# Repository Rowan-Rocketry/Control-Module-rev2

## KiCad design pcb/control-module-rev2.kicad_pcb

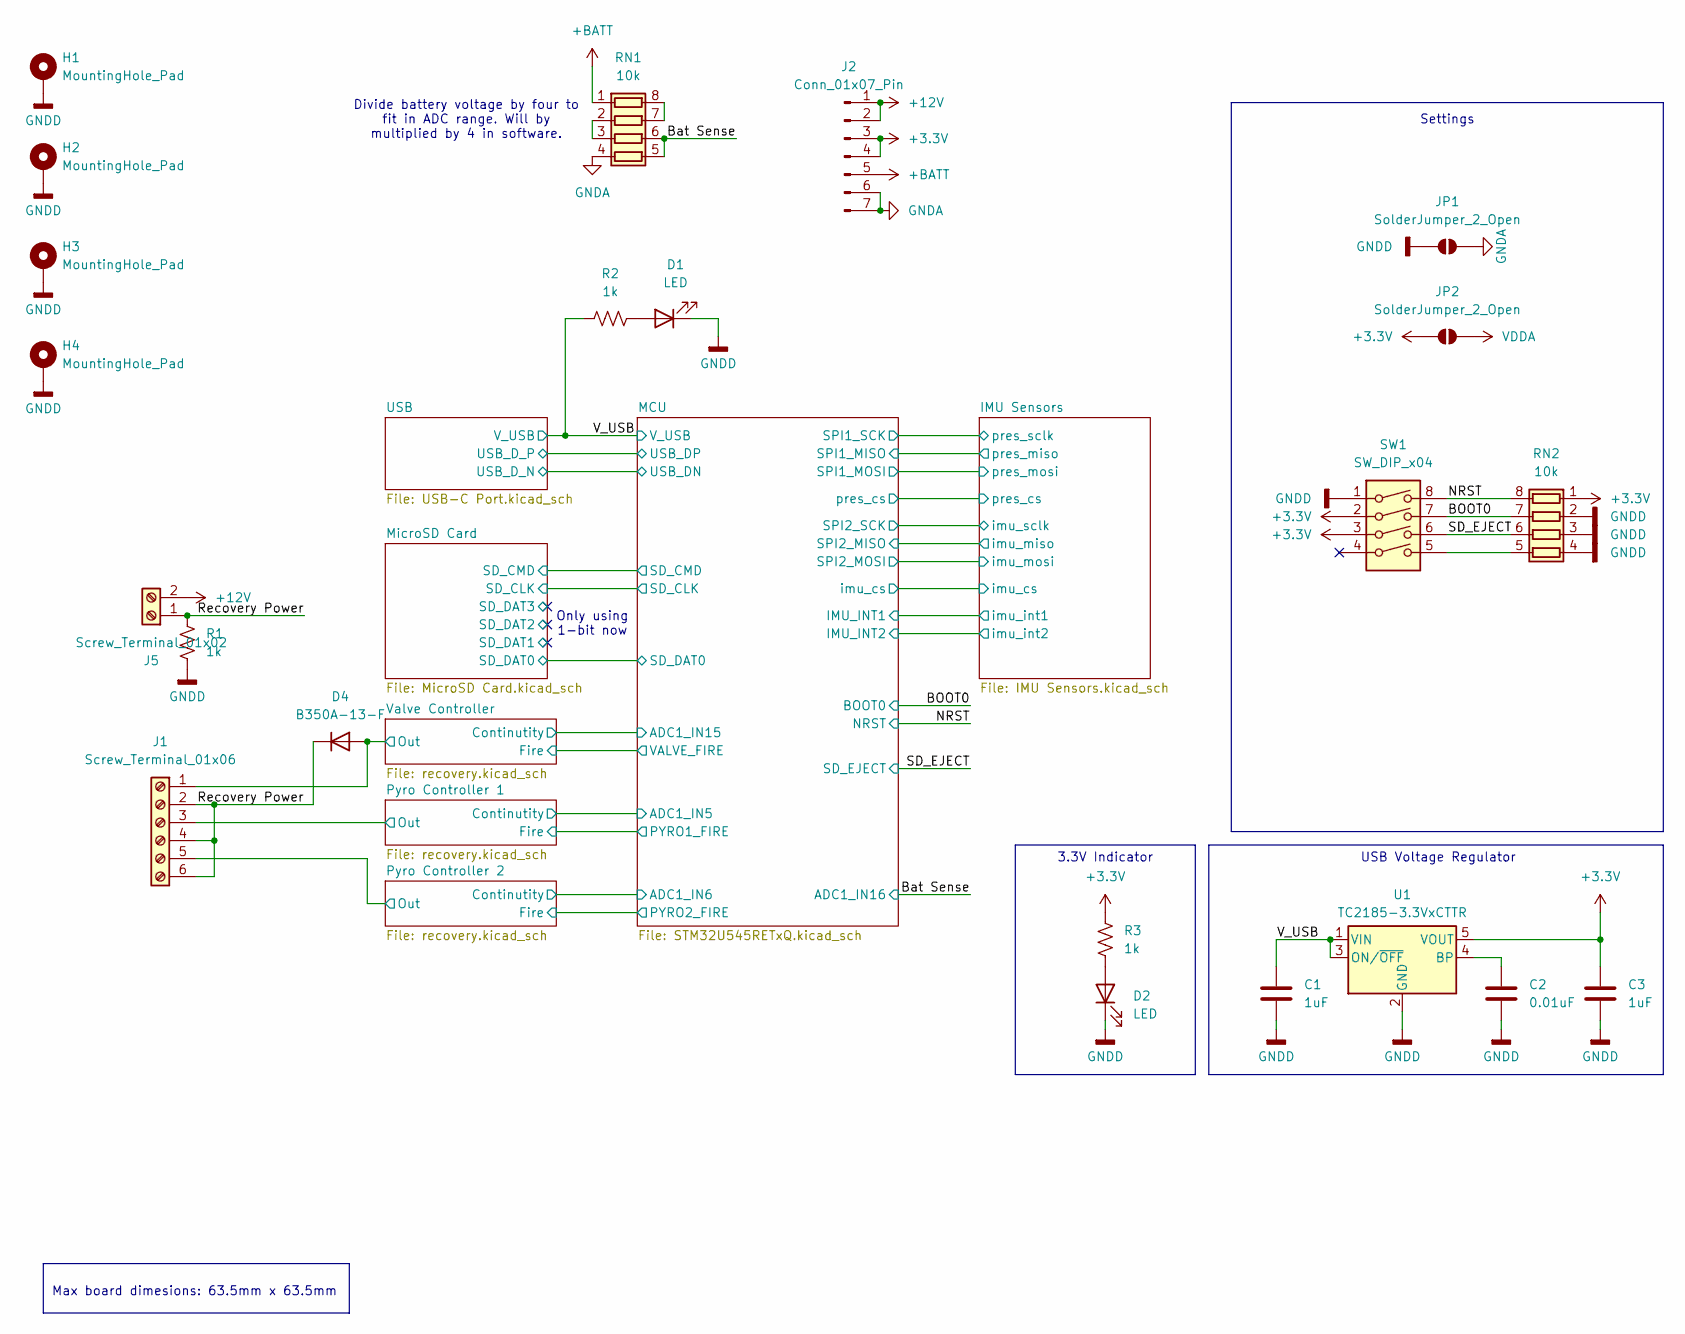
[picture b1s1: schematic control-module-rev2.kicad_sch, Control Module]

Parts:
C1, C3: 1uF; C_0603_1608Metric
C2: 0.01uF; C_0603_1608Metric
D1, D2: LED; LED_0603_1608Metric
D4: B350A-13-F; D_SOD-123F
H1, H2, H3, H4: MountingHole_Pad; MountingHole_3.2mm_M3_Pad_Via
J1: Screw_Terminal_01x06; TerminalBlock_Phoenix_MPT-0,5-6-2.54_1x06_P2.54mm_Horizontal
J2: Conn_01x07_Pin; PinHeader_1x07_P2.54mm_Vertical
J5: Screw_Terminal_01x02; TerminalBlock_Phoenix_MPT-0,5-2-2.54_1x02_P2.54mm_Horizontal
JP1, JP2: SolderJumper_2_Open; SolderJumper-2_P1.3mm_Open_RoundedPad1.0x1.5mm
R1, R2, R3: 1k; R_0603_1608Metric
RN1, RN2: 10k; R_Array_Convex_4x0612
SW1: SW_DIP_x04; SW_DIP_SPSTx04_Slide_Copal_CHS-04A_W5.08mm_P1.27mm_JPin
U1: TC2185-3.3VxCTTR; SOT-23-5

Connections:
+3.3V: C3.1, J2.3, J2.4, JP2.1 (A), R3.1, RN2.1 (R1.1), SW1.2, SW1.3, U1.5 (VOUT); also elsewhere on the board
+12V: J2.1, J2.2, J5.2
+BATT: J2.5, RN1.1 (R1.1)
/BOOT0: RN2.7 (R2.2), SW1.7; also elsewhere on the board
/Bat Sense: RN1.5 (R4.2), RN1.6 (R3.2); also elsewhere on the board
/NRST: RN2.8 (R1.2), SW1.8; also elsewhere on the board
/Pyro Controller 1/Out: J1.3; also elsewhere on the board
/Pyro Controller 2/Out: J1.5; also elsewhere on the board
/Recovery Power: D4.1 (K), J1.2, J1.4, J1.6, J5.1, R1.2
/SD_EJECT: RN2.6 (R3.2), SW1.6; also elsewhere on the board
/V_USB: C1.1, R2.1, U1.1 (VIN), U1.3 (ON/~OFF); also elsewhere on the board
/Valve Controller/Out: D4.2 (A), J1.1; also elsewhere on the board
GNDA: J2.6, J2.7, JP1.2 (B), RN1.4 (R4.1); also elsewhere on the board
GNDD: C1.2, C2.2, C3.2, D1.1 (K), D2.1 (K), H1.1, H2.1, H3.1, H4.1, JP1.1 (A), R1.1, RN2.2 (R2.1), RN2.3 (R3.1), RN2.4 (R4.1), SW1.1, U1.2 (GND); also elsewhere on the board
unnamed: D1.2 (A), R2.2
unnamed: D2.2 (A), R3.2
unnamed: RN1.7 (R2.2), RN1.8 (R1.2)
unnamed: RN1.2 (R2.1), RN1.3 (R3.1)
unnamed: RN2.5 (R4.2), SW1.5
unnamed: C2.1, U1.4 (BP)
VDDA: JP2.2 (B); also elsewhere on the board

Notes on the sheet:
Settings
Max board dimesions: 63.5mm x 63.5mm
Divide battery voltage by four to fit in ADC range. Will by multiplied by 4 in software.
3.3V Indicator
Only using 1-bit now
USB Voltage Regulator

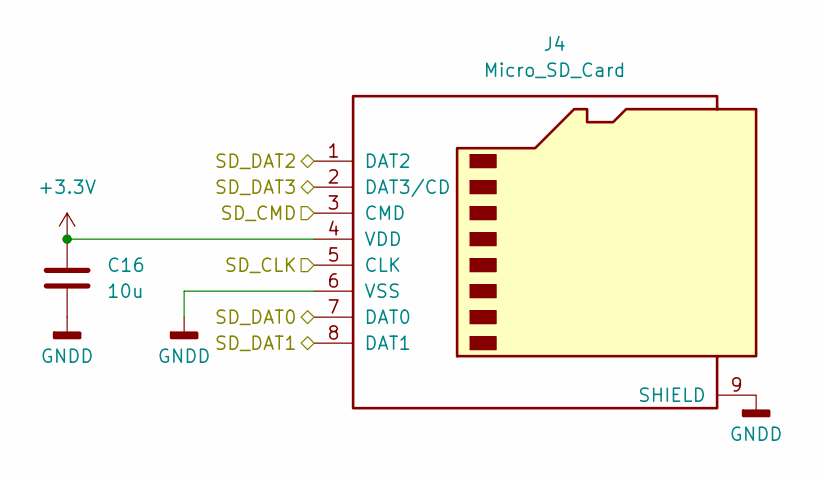
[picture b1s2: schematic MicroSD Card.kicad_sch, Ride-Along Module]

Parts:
C16: 10u; C_0603_1608Metric_Pad1.08x0.95mm_HandSolder
J4: Micro_SD_Card; microSD_HC_Molex_47219-2001

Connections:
+3.3V: C16.1, J4.4 (VDD); also elsewhere on the board
/MCU/SD_CLK: J4.5 (CLK); also elsewhere on the board
/MCU/SD_CMD: J4.3 (CMD); also elsewhere on the board
/MCU/SD_DAT0: J4.7 (DAT0); also elsewhere on the board
/MicroSD Card/SD_DAT1: J4.8 (DAT1)
/MicroSD Card/SD_DAT2: J4.1 (DAT2)
/MicroSD Card/SD_DAT3: J4.2 (DAT3/CD)
GNDD: C16.2, J4.6 (VSS), J4.9 (SHIELD); also elsewhere on the board

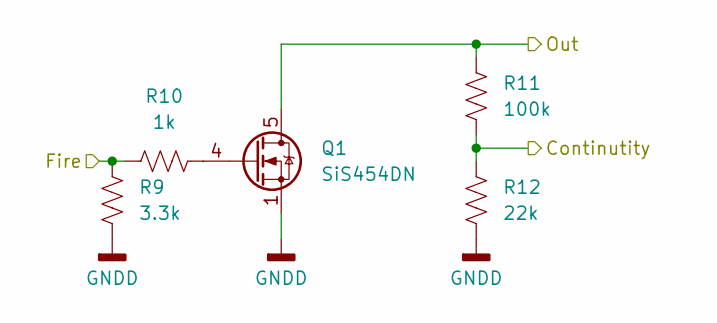
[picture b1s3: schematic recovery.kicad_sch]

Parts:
Q1: SiS454DN; Vishay_PowerPAK_1212-8_Single
R9: 3.3k; R_0603_1608Metric_Pad0.98x0.95mm_HandSolder
R10: 1k; R_0603_1608Metric_Pad0.98x0.95mm_HandSolder
R11: 100k; R_0603_1608Metric_Pad0.98x0.95mm_HandSolder
R12: 22k; R_0603_1608Metric_Pad0.98x0.95mm_HandSolder

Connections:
/MCU/ADC1_IN6: R11.1, R12.2; also elsewhere on the board
/MCU/PYRO2_FIRE: R9.2, R10.1; also elsewhere on the board
/Pyro Controller 2/Out: Q1.5 (D), R11.2; also elsewhere on the board
GNDD: Q1.1 (S), Q1.2 (S), Q1.3 (S), R9.1, R12.1; also elsewhere on the board
unnamed: Q1.4 (G), R10.2

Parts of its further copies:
Q2, Q3: SiS454DN; Vishay_PowerPAK_1212-8_Single
R13, R17: 3.3k; R_0603_1608Metric_Pad0.98x0.95mm_HandSolder
R14, R18: 1k; R_0603_1608Metric_Pad0.98x0.95mm_HandSolder
R15, R19: 100k; R_0603_1608Metric_Pad0.98x0.95mm_HandSolder
R16, R20: 22k; R_0603_1608Metric_Pad0.98x0.95mm_HandSolder

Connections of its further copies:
/MCU/ADC1_IN5: R19.1, R20.2; also elsewhere on the board
/MCU/ADC1_IN15: R15.1, R16.2; also elsewhere on the board
/MCU/PYRO1_FIRE: R17.2, R18.1; also elsewhere on the board
/MCU/VALVE_FIRE: R13.2, R14.1; also elsewhere on the board
/Pyro Controller 1/Out: Q3.5 (D), R19.2; also elsewhere on the board
/Valve Controller/Out: Q2.5 (D), R15.2; also elsewhere on the board
GNDD: Q2.1 (S), Q2.2 (S), Q2.3 (S), Q3.1 (S), Q3.2 (S), Q3.3 (S), R13.1, R16.1, R17.1, R20.1; also elsewhere on the board
unnamed: Q2.4 (G), R14.2
unnamed: Q3.4 (G), R18.2

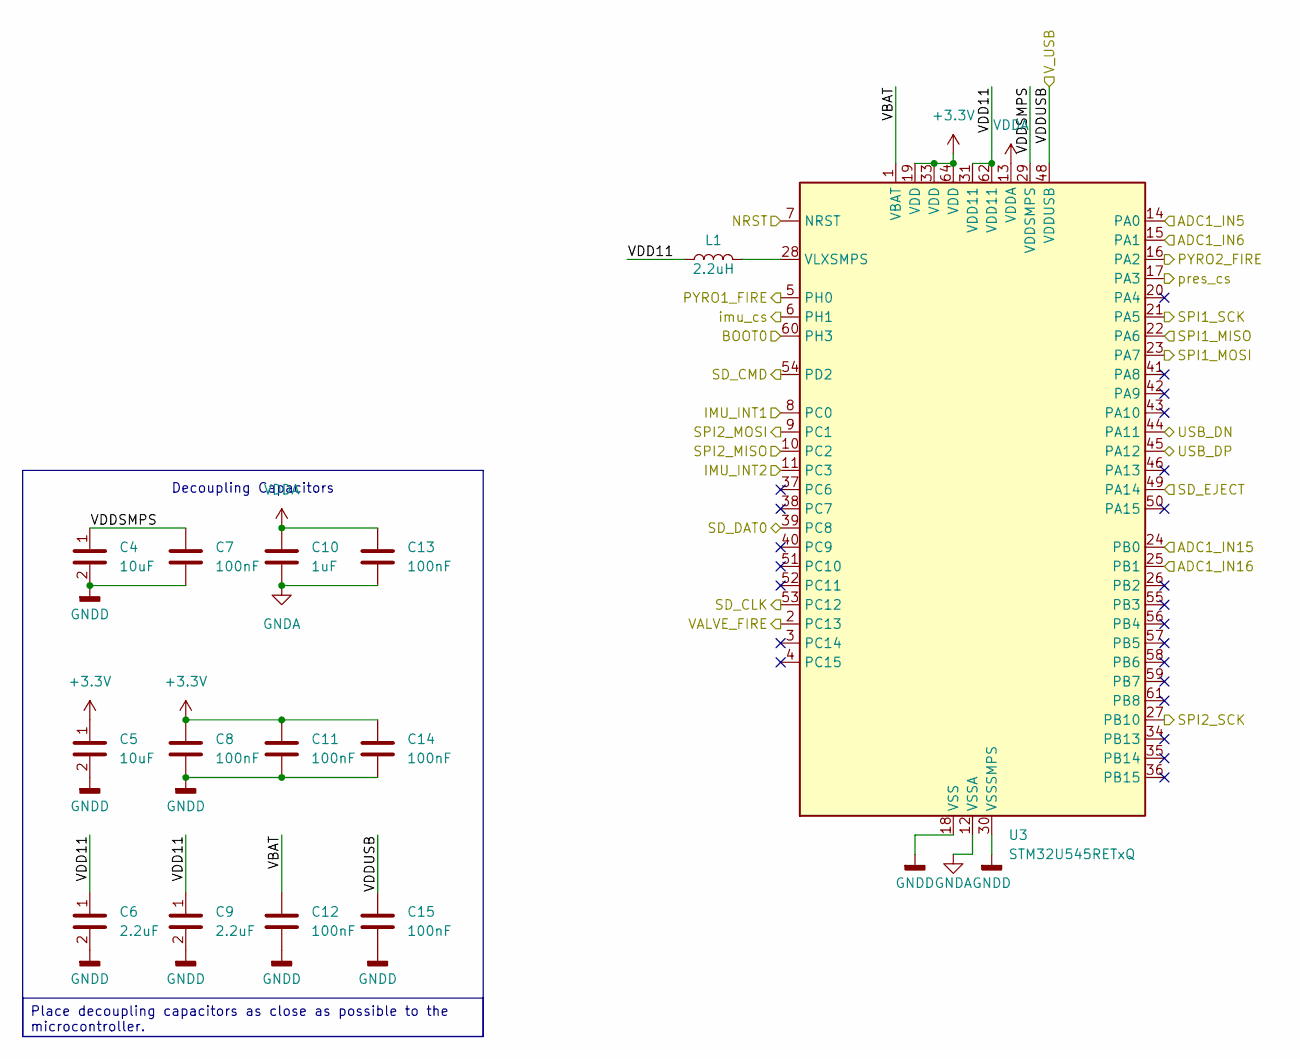
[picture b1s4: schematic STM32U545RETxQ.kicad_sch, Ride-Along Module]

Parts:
C4, C5: 10uF; C_0603_1608Metric_Pad1.08x0.95mm_HandSolder
C6, C9: 2.2uF; C_0603_1608Metric_Pad1.08x0.95mm_HandSolder
C7, C8, C11, C12, C13, C14, C15: 100nF; C_0603_1608Metric_Pad1.08x0.95mm_HandSolder
C10: 1uF; C_0603_1608Metric_Pad1.08x0.95mm_HandSolder
L1: 2.2uH; L_0603_1608Metric_Pad1.05x0.95mm_HandSolder
U3: STM32U545RETxQ; LQFP-64_10x10mm_P0.5mm

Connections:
+3.3V: C5.1, C8.1, C11.1, C14.1, U3.19 (VDD), U3.33 (VDD), U3.64 (VDD); also elsewhere on the board
/BOOT0: U3.60 (PH3); also elsewhere on the board
/Bat Sense: U3.25 (PB1); also elsewhere on the board
/IMU Sensors/imu_cs: U3.6 (PH1); also elsewhere on the board
/IMU Sensors/imu_int1: U3.8 (PC0); also elsewhere on the board
/IMU Sensors/imu_int2: U3.11 (PC3); also elsewhere on the board
/IMU Sensors/imu_miso: U3.10 (PC2); also elsewhere on the board
/IMU Sensors/imu_mosi: U3.9 (PC1); also elsewhere on the board
/IMU Sensors/imu_sclk: U3.27 (PB10); also elsewhere on the board
/IMU Sensors/pres_cs: U3.17 (PA3); also elsewhere on the board
/IMU Sensors/pres_miso: U3.22 (PA6); also elsewhere on the board
/IMU Sensors/pres_mosi: U3.23 (PA7); also elsewhere on the board
/IMU Sensors/pres_sclk: U3.21 (PA5); also elsewhere on the board
/MCU/ADC1_IN5: U3.14 (PA0); also elsewhere on the board
/MCU/ADC1_IN6: U3.15 (PA1); also elsewhere on the board
/MCU/ADC1_IN15: U3.24 (PB0); also elsewhere on the board
/MCU/PYRO1_FIRE: U3.5 (PH0); also elsewhere on the board
/MCU/PYRO2_FIRE: U3.16 (PA2); also elsewhere on the board
/MCU/SD_CLK: U3.53 (PC12); also elsewhere on the board
/MCU/SD_CMD: U3.54 (PD2); also elsewhere on the board
/MCU/SD_DAT0: U3.39 (PC8); also elsewhere on the board
/MCU/USB_DN: U3.44 (PA11); also elsewhere on the board
/MCU/USB_DP: U3.45 (PA12); also elsewhere on the board
/MCU/VALVE_FIRE: U3.2 (PC13); also elsewhere on the board
/MCU/VBAT: C12.1, U3.1 (VBAT)
/MCU/VDD11: C6.1, C9.1, L1.1, U3.31 (VDD11), U3.62 (VDD11)
/MCU/VDDSMPS: C4.1, C7.1, U3.29 (VDDSMPS)
/NRST: U3.7 (NRST); also elsewhere on the board
/SD_EJECT: U3.49 (PA14); also elsewhere on the board
/V_USB: C15.1, U3.48 (VDDUSB); also elsewhere on the board
GNDA: C10.2, C13.2, U3.12 (VSSA); also elsewhere on the board
GNDD: C4.2, C5.2, C6.2, C7.2, C8.2, C9.2, C11.2, C12.2, C14.2, C15.2, U3.18 (VSS), U3.30 (VSSSMPS), U3.32 (VSS), U3.47 (VSS), U3.63 (VSS); also elsewhere on the board
unnamed: L1.2, U3.28 (VLXSMPS)
VDDA: C10.1, C13.1, U3.13 (VDDA); also elsewhere on the board

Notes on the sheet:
Decoupling Capacitors
Place decoupling capacitors as close as possible to the microcontroller.

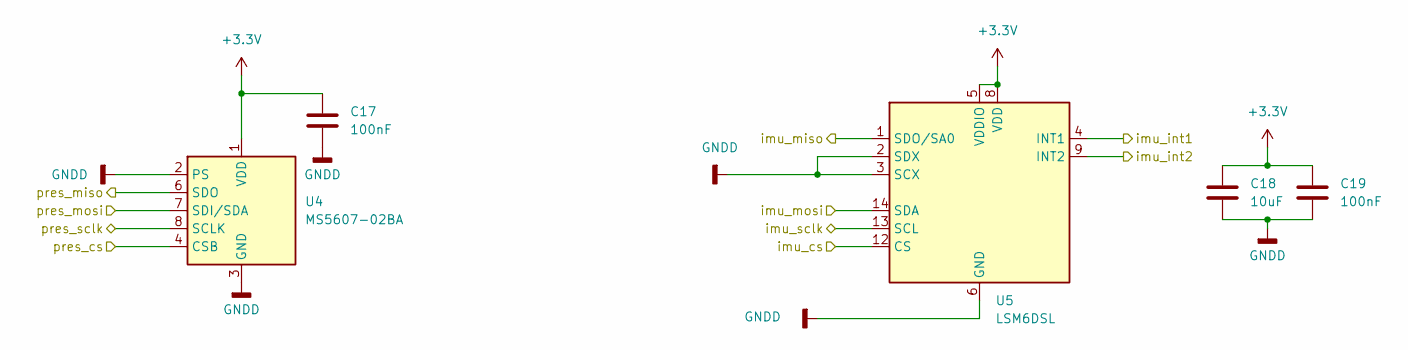
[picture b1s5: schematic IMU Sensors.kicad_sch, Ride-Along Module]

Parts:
C17, C19: 100nF; C_0603_1608Metric_Pad1.08x0.95mm_HandSolder
C18: 10uF; C_0603_1608Metric_Pad1.08x0.95mm_HandSolder
U4: MS5607-02BA; LGA-8_3x5mm_P1.25mm
U5: LSM6DSL; LGA-14_3x2.5mm_P0.5mm_LayoutBorder3x4y

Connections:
+3.3V: C17.1, C18.1, C19.1, U4.1 (VDD), U5.5 (VDDIO), U5.8 (VDD); also elsewhere on the board
/IMU Sensors/imu_cs: U5.12 (CS); also elsewhere on the board
/IMU Sensors/imu_int1: U5.4 (INT1); also elsewhere on the board
/IMU Sensors/imu_int2: U5.9 (INT2); also elsewhere on the board
/IMU Sensors/imu_miso: U5.1 (SDO/SA0); also elsewhere on the board
/IMU Sensors/imu_mosi: U5.14 (SDA); also elsewhere on the board
/IMU Sensors/imu_sclk: U5.13 (SCL); also elsewhere on the board
/IMU Sensors/pres_cs: U4.4 (CSB), U4.5 (CSB); also elsewhere on the board
/IMU Sensors/pres_miso: U4.6 (SDO); also elsewhere on the board
/IMU Sensors/pres_mosi: U4.7 (SDI/SDA); also elsewhere on the board
/IMU Sensors/pres_sclk: U4.8 (SCLK); also elsewhere on the board
GNDD: C17.2, C18.2, C19.2, U4.2 (PS), U4.3 (GND), U5.2 (SDX), U5.3 (SCX), U5.6 (GND), U5.7 (GND); also elsewhere on the board

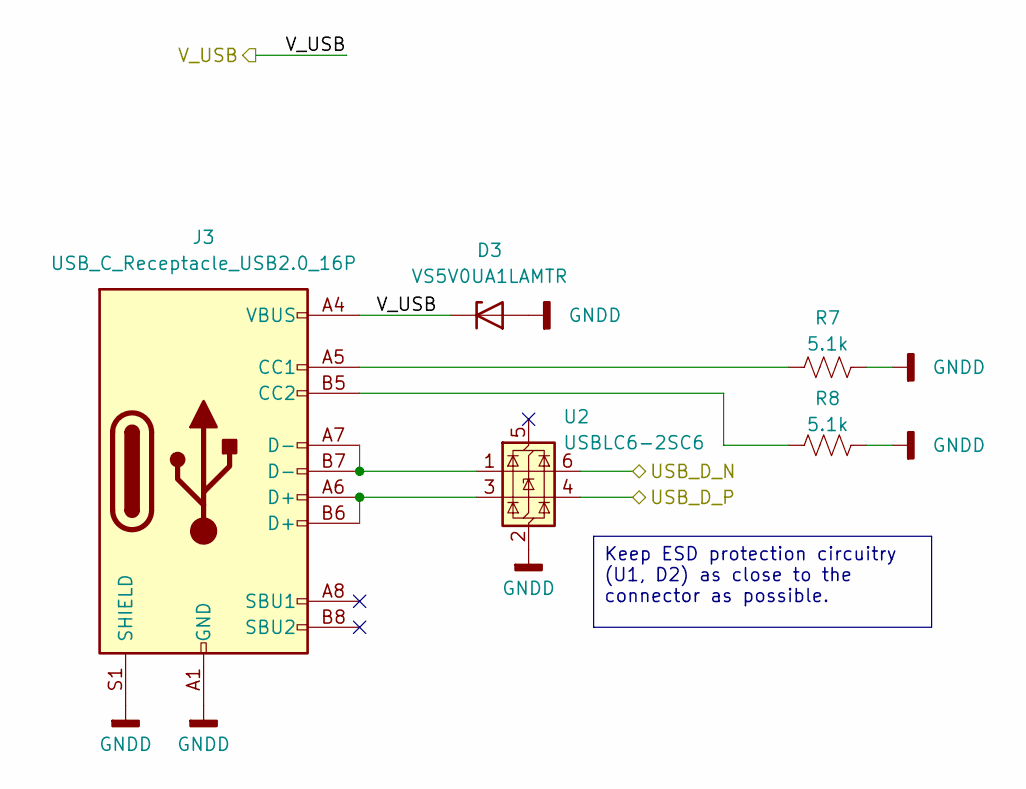
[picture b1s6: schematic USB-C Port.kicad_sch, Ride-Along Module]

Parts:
D3: VS5V0UA1LAMTR; D_SOD-128
J3: USB_C_Receptacle_USB2.0_16P; USB_C_Receptacle_GCT_USB4105-xx-A_16P_TopMnt_Horizontal
R7, R8: 5.1k; R_0603_1608Metric
U2: USBLC6-2SC6; SOT-23-6

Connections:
/MCU/USB_DN: U2.6 (I/O1); also elsewhere on the board
/MCU/USB_DP: U2.4 (I/O2); also elsewhere on the board
/V_USB: D3.1 (K), J3.A4 (VBUS), J3.A9 (VBUS), J3.B4 (VBUS), J3.B9 (VBUS); also elsewhere on the board
GNDD: D3.2 (A), J3.A1 (GND), J3.A12 (GND), J3.B1 (GND), J3.B12 (GND), J3.S1 (SHIELD), R7.2, R8.2, U2.2 (GND); also elsewhere on the board
unnamed: J3.A5 (CC1), R7.1
unnamed: J3.B5 (CC2), R8.1
unnamed: J3.A6 (D+), J3.B6 (D+), U2.3 (I/O2)
unnamed: J3.A7 (D-), J3.B7 (D-), U2.1 (I/O1)

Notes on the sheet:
Keep ESD protection circuitry (U1, D2) as close to the connector as possible.

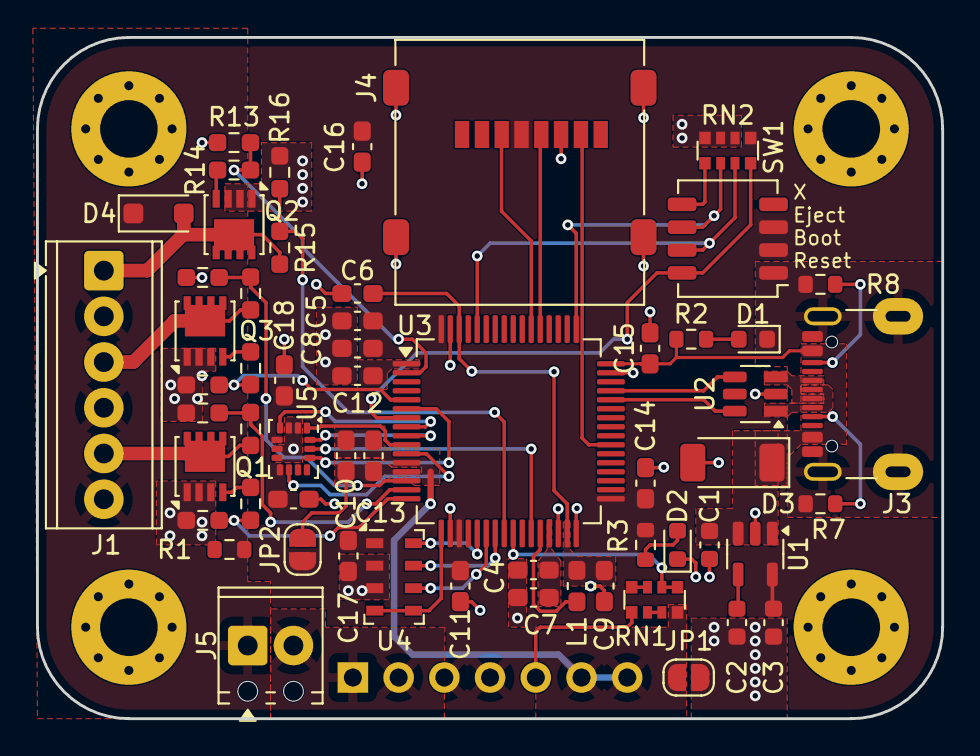
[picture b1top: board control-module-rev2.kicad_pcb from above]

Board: 2 copper layers, 50.3 x 37.8 mm, 63 parts (1 on the bottom side), 53 nets.

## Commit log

2025-09-18 Initial copy of control module rev1
    New repo for control module rev2 is starting with final kicad files from rev1. Rev1 repo will remain in its present state as an archive
2025-09-18 Organization
    Bringing kicad files from unneeded lower level file into pcb file
2025-09-18 Sync
    Sync
2026-02-05 Labeled max board dimensions in root sch
